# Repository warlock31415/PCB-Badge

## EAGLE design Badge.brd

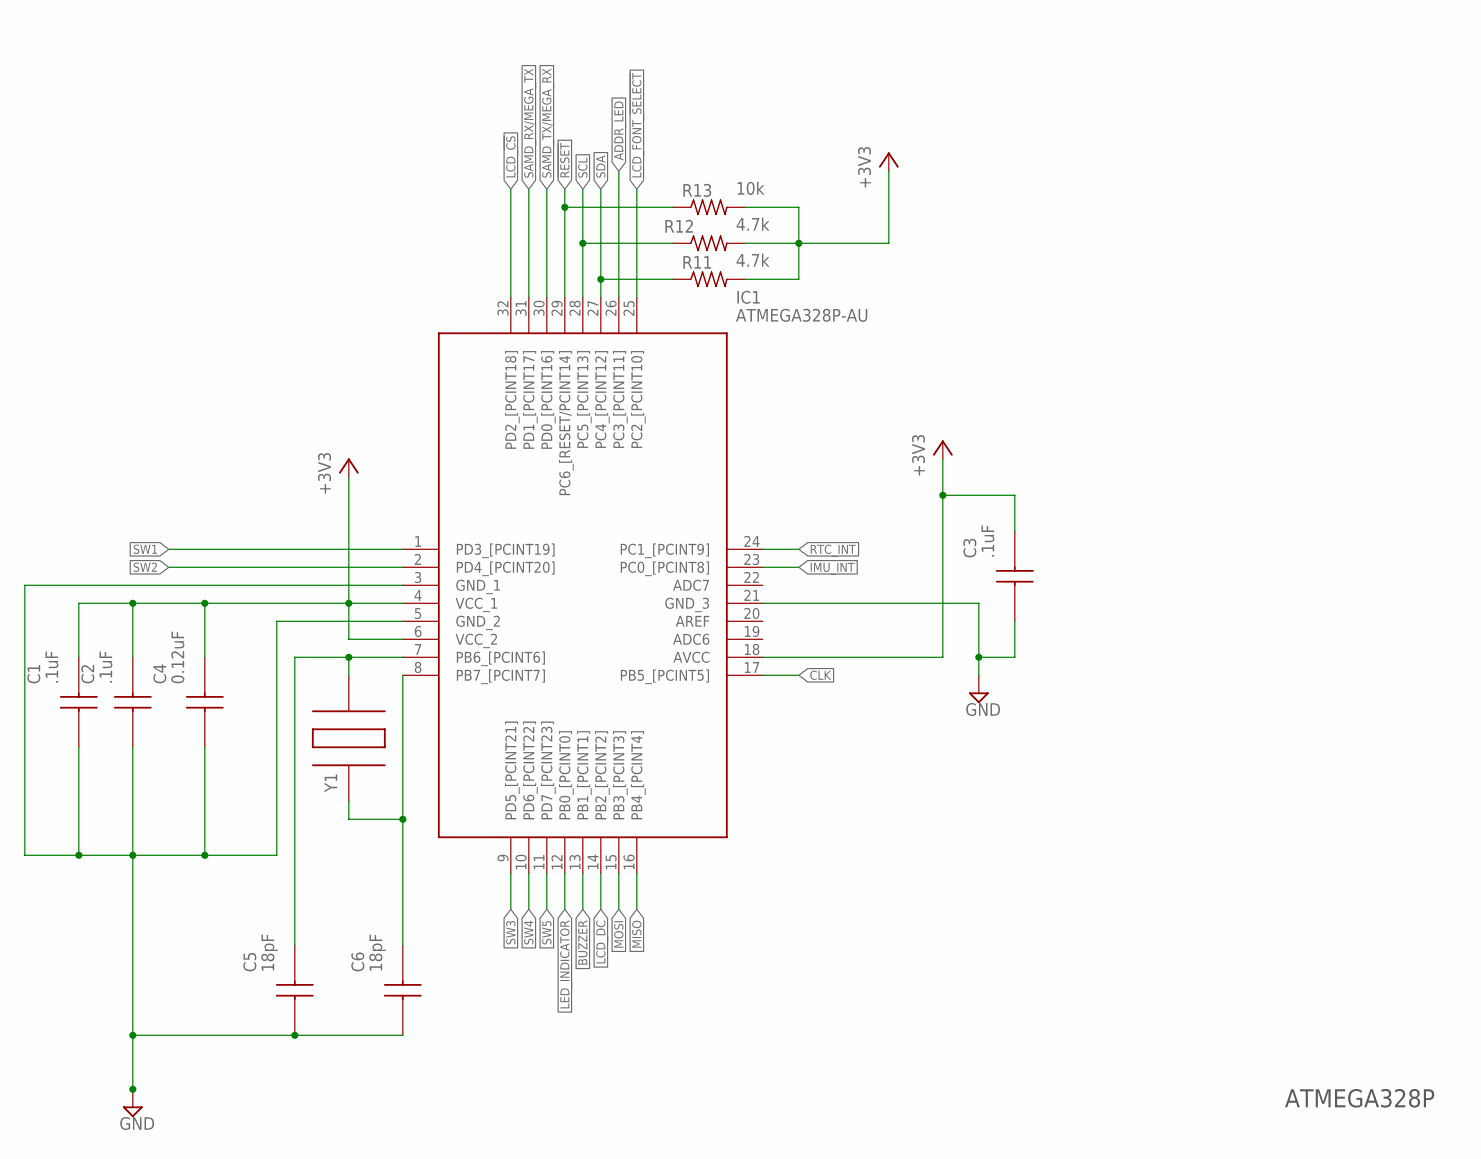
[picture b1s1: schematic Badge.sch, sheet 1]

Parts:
C1, C2, C3: .1uF; CAPC1608X87N
C4: 0.12uF; CAPC2013X94N
C5, C6: 18pF; CAPC1608X87N
IC1: ATMEGA328P-AU; QFP80P900X900X120-32N
R11: 4.7k; R0603; MANUFACTURER_PART_NUMBER o RC0603JR-074K7L
R12: 4.7k; R0603
R13: 10k; R0603; MANUFACTURER_PART_NUMBER RC0603JR-0710KL
Y1: ABM3-16.000MHZ-B2-T; ABM-3

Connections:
!RESET!: IC1.29 (PC6_[RESET/PCINT14]), R13.1; also elsewhere on the board
+3V3: C1.2, C2.2, C3.2, C4.2 (C2), IC1.4 (VCC_1), IC1.6 (VCC_2), IC1.18 (AVCC), R11.2, R12.2, R13.2; also elsewhere on the board
ADDR_LED: IC1.26 (PC3_[PCINT11]); also elsewhere on the board
BUZZER: IC1.13 (PB1_[PCINT1]); also elsewhere on the board
CLK: IC1.17 (PB5_[PCINT5])
GND: C1.1, C2.1, C3.1, C4.1 (C1), C5.1, C6.1, IC1.3 (GND_1), IC1.5 (GND_2), IC1.21 (GND_3); also elsewhere on the board
IMU_INT: IC1.23 (PC0_[PCINT8]); also elsewhere on the board
LCD_!CS!: IC1.32 (PD2_[PCINT18])
LCD_DC: IC1.14 (PB2_[PCINT2])
LCD_FONT_!SELECT!: IC1.25 (PC2_[PCINT10])
LED_INDICATOR: IC1.12 (PB0_[PCINT0]); also elsewhere on the board
MISO: IC1.16 (PB4_[PCINT4])
MOSI: IC1.15 (PB3_[PCINT3])
unnamed: C5.2, IC1.7 (PB6_[PCINT6]), Y1.2
unnamed: C6.2, IC1.8 (PB7_[PCINT7]), Y1.1
RTC_INT: IC1.24 (PC1_[PCINT9]); also elsewhere on the board
SAMD_RX/MEGA_TX: IC1.31 (PD1_[PCINT17]); also elsewhere on the board
SAMD_TX/MEGA_RX: IC1.30 (PD0_[PCINT16]); also elsewhere on the board
SCL: IC1.28 (PC5_[PCINT13]), R12.1; also elsewhere on the board
SDA: IC1.27 (PC4_[PCINT12]), R11.1; also elsewhere on the board
SW1: IC1.1 (PD3_[PCINT19]); also elsewhere on the board
SW2: IC1.2 (PD4_[PCINT20]); also elsewhere on the board
SW3: IC1.9 (PD5_[PCINT21]); also elsewhere on the board
SW4: IC1.10 (PD6_[PCINT22]); also elsewhere on the board
SW5: IC1.11 (PD7_[PCINT23]); also elsewhere on the board

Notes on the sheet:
ATMEGA328P

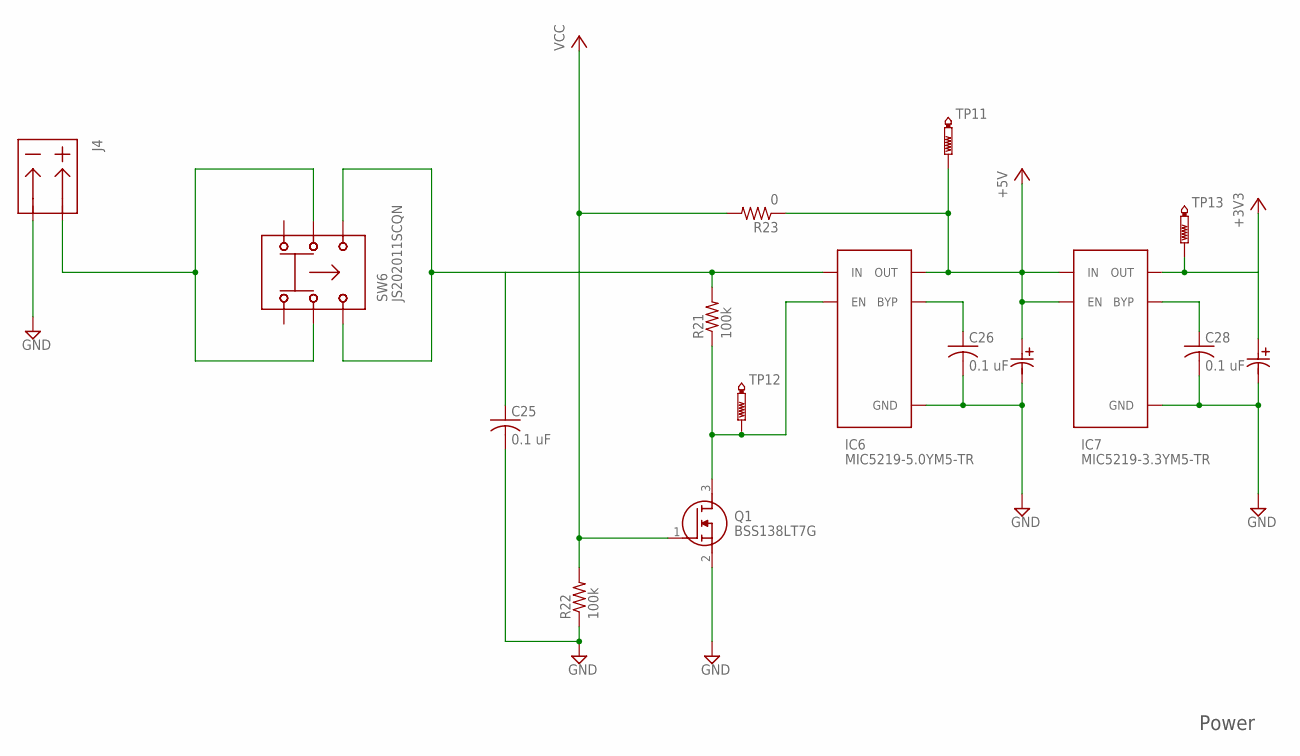
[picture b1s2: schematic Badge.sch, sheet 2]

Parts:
C25, C26, C28: 0.1 uF; C0603K
C27, C29: 22uF 16V 4.3mm; CAPAE430X550L180X65N
IC6: MIC5219-5.0YM5-TR; SOT23-5P95_280X145L45X37N
IC7: MIC5219-3.3YM5-TR; SOT23-5P95_280X145L45X37N
J4: DNP; BATIN
Q1: BSS138LT7G; SOT96P237X111-3N
R21, R22: 100k; R0603
R23: 0; R0603
SW6: JS202011SCQN
TP11, TP12, TP13: PTR1PAD1-20; P1-20

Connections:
+5V: C27.1 (PLUS), IC6.5 (OUT), IC7.1 (IN), IC7.3 (EN), R23.1, TP11.TP; also elsewhere on the board
+5V1: C29.1 (PLUS), IC7.5 (OUT), TP13.TP
GND: C25.2, C26.2, C27.2 (MINUS), C28.2, C29.2 (MINUS), IC6.2 (GND), IC7.2 (GND), J4.2, Q1.2 (S), R22.1; also elsewhere on the board
unnamed: C26.1, IC6.4 (BYP)
unnamed: C28.1, IC7.4 (BYP)
unnamed: J4.1, SW6.2, SW6.5
unnamed: C25.1, IC6.1 (IN), R21.2, SW6.3, SW6.6
unnamed: IC6.3 (EN), Q1.3 (D), R21.1, TP12.TP
VCC: Q1.1 (G), R22.2, R23.2

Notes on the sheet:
Power

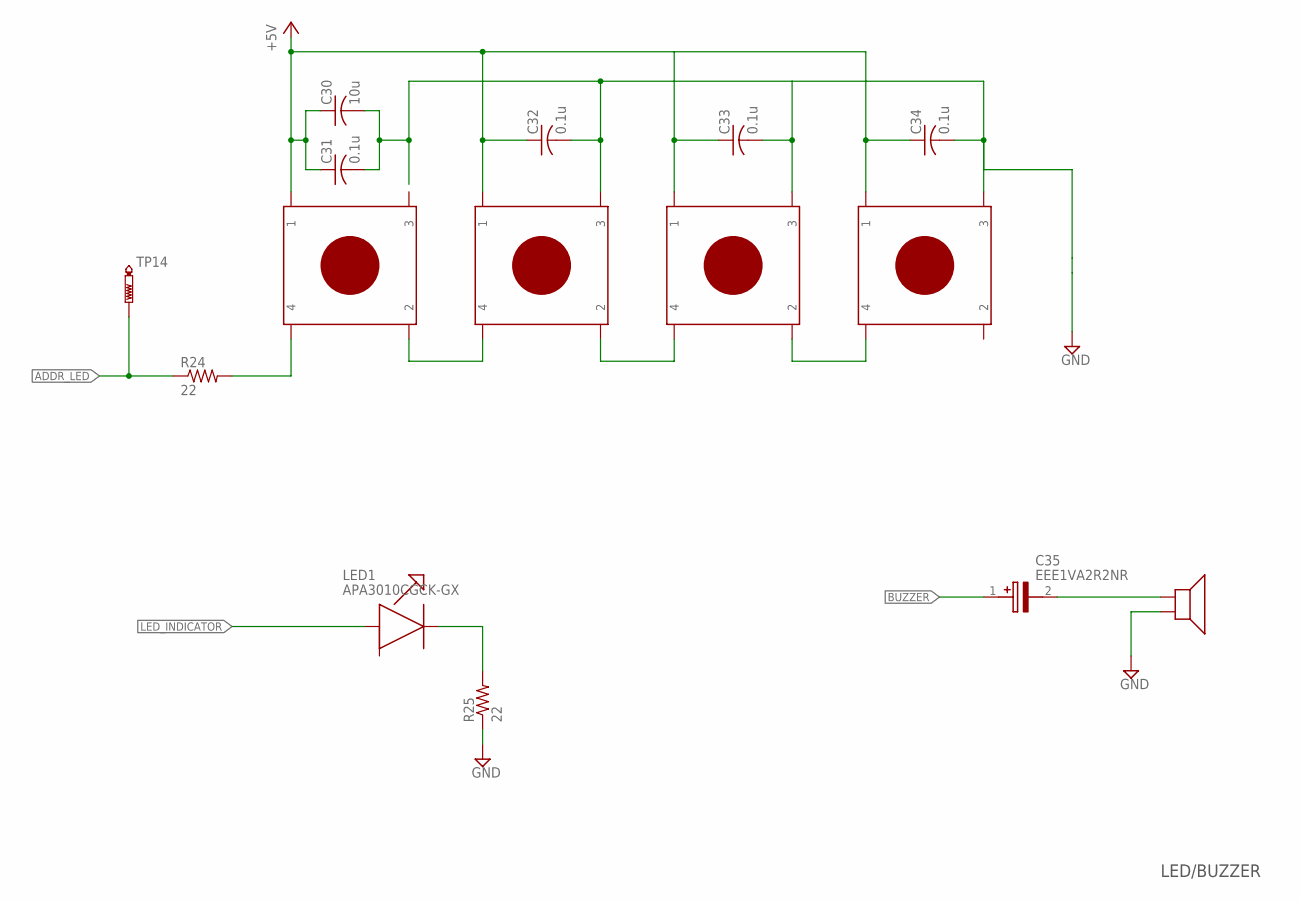
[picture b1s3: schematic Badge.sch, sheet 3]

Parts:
C30: 10u; C0805K
C31, C32, C33, C34: 0.1u; C0603K
C35: EEE1VA2R2NR; CAPAE430X550N
D2, D3, D4, D5: WS2812B
LED1: APA3010CGCK-GX; APA3010ZGCGX
LS1: AST-03008MR-R; PUIAUDIO_AST-03008MR-R
R24, R25: 22; R0603
TP14: PTR1PAD1-20; P1-20

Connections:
+5V: C30.1, C31.1, C32.1, C33.1, C34.1, D2.1, D3.1, D4.1, D5.1; also elsewhere on the board
ADDR_LED: R24.1, TP14.TP; also elsewhere on the board
BUZZER: C35.1 (+); also elsewhere on the board
GND: C30.2, C31.2, C32.2, C33.2, C34.2, D3.3, D4.3, D5.3, LS1.2, R25.1; also elsewhere on the board
LED_INDICATOR: LED1.2 (A); also elsewhere on the board
unnamed: C35.2 (-), LS1.1
unnamed: LED1.1 (K), R25.2
unnamed: D2.2, D3.4
unnamed: D3.2, D4.4
unnamed: D4.2, D5.4
unnamed: D2.4, R24.2

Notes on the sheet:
LED/BUZZER

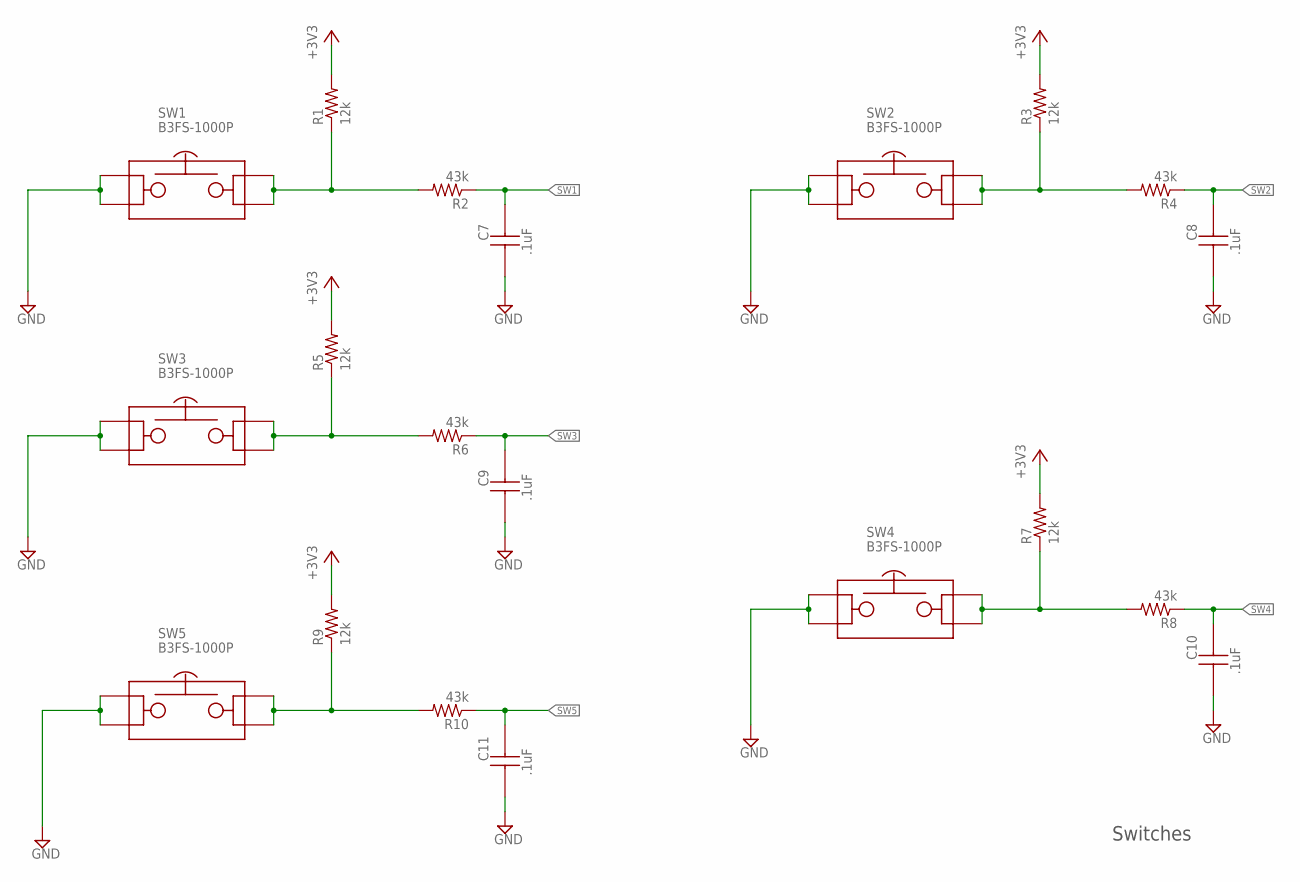
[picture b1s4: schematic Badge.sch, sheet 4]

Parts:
C7, C8, C9, C10, C11: .1uF; CAPC1608X87N
R1, R3, R5, R7, R9: 12k; R0603; MANUFACTURER_PART_NUMBER RC0603JR-0712KL
R2, R4, R6, R8, R10: 43k; R0603; MANUFACTURER_PART_NUMBER RC0603JR-0743KL
SW1, SW2, SW3, SW4, SW5: B3FS-1000P

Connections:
+3V3: R1.2, R3.2, R5.2, R7.2, R9.2; also elsewhere on the board
GND: C7.1, C8.1, C9.1, C10.1, C11.1, SW1.P$1, SW1.P$2, SW2.P$1, SW2.P$2, SW3.P$1, SW3.P$2, SW4.P$1, SW4.P$2, SW5.P$1, SW5.P$2; also elsewhere on the board
unnamed: R1.1, R2.2, SW1.P$3, SW1.P$4
unnamed: R5.1, R6.2, SW3.P$3, SW3.P$4
unnamed: R7.1, R8.2, SW4.P$3, SW4.P$4
unnamed: R3.1, R4.2, SW2.P$3, SW2.P$4
unnamed: R9.1, R10.2, SW5.P$3, SW5.P$4
SW1: C7.2, R2.1; also elsewhere on the board
SW2: C8.2, R4.1; also elsewhere on the board
SW3: C9.2, R6.1; also elsewhere on the board
SW4: C10.2, R8.1; also elsewhere on the board
SW5: C11.2, R10.1; also elsewhere on the board

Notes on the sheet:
Switches

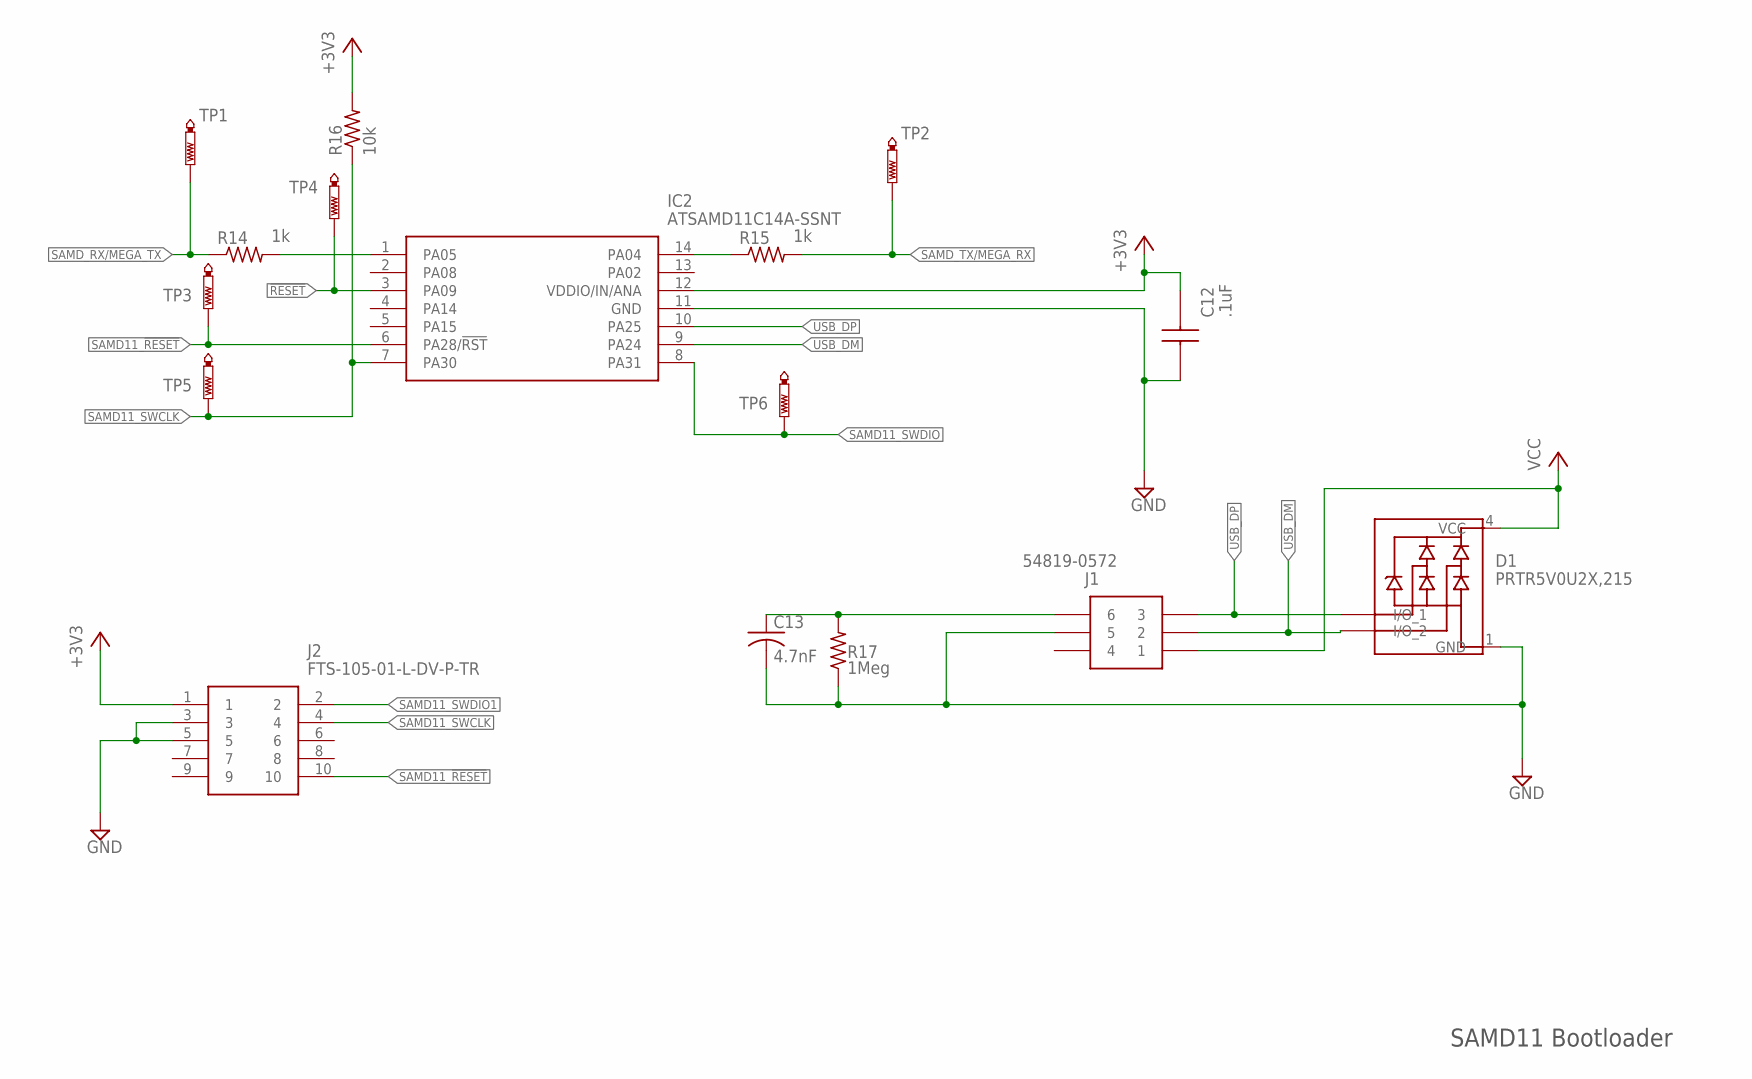
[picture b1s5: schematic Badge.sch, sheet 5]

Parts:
C12: .1uF; CAPC1608X87N
C13: 4.7nF; C0805K
D1: PRTR5V0U2X,215; SOT-143B
IC2: ATSAMD11C14A-SSNT; SOIC127P600X175-14N
J1: 54819-0572; MOLEXMINIBTYPEB_1
J2: FTS-105-01-L-DV-P-TR; FTS10501LDVPTR
R14, R15: 1k; R0603; MANUFACTURER_PART_NUMBER RC0603JR-0710KL
R16: 10k; R0603; MANUFACTURER_PART_NUMBER RC0603JR-0710KL
R17: 1Meg; R0603
TP1, TP2, TP3, TP4, TP5, TP6: PTR1PAD1-20; P1-20

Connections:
!RESET!: IC2.3 (PA09), TP4.TP; also elsewhere on the board
+3V3: C12.2, IC2.12 (VDDIO/IN/ANA), J2.1, R16.2; also elsewhere on the board
GND: C12.1, C13.2, D1.1 (GND), IC2.11 (GND), J1.5, J2.3, J2.5, R17.1; also elsewhere on the board
unnamed: IC2.14 (PA04), R15.1
unnamed: IC2.1 (PA05), R14.2
unnamed: C13.1, J1.6, J1.7 (6), J1.8 (6), J1.9 (6), R17.2
SAMD11_!RESET!: IC2.6 (PA28/!RST), J2.10, TP3.TP
SAMD11_SWCLK: IC2.7 (PA30), J2.4, R16.1, TP5.TP
SAMD11_SWDIO: IC2.8 (PA31), TP6.TP
SAMD11_SWDIO1: J2.2
SAMD_RX/MEGA_TX: R14.1, TP1.TP; also elsewhere on the board
SAMD_TX/MEGA_RX: R15.2, TP2.TP; also elsewhere on the board
USB_DM: D1.3 (I/O_2), IC2.9 (PA24), J1.2
USB_DP: D1.2 (I/O_1), IC2.10 (PA25), J1.3
V_USB: D1.4 (VCC), J1.1

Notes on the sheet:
SAMD11 Bootloader

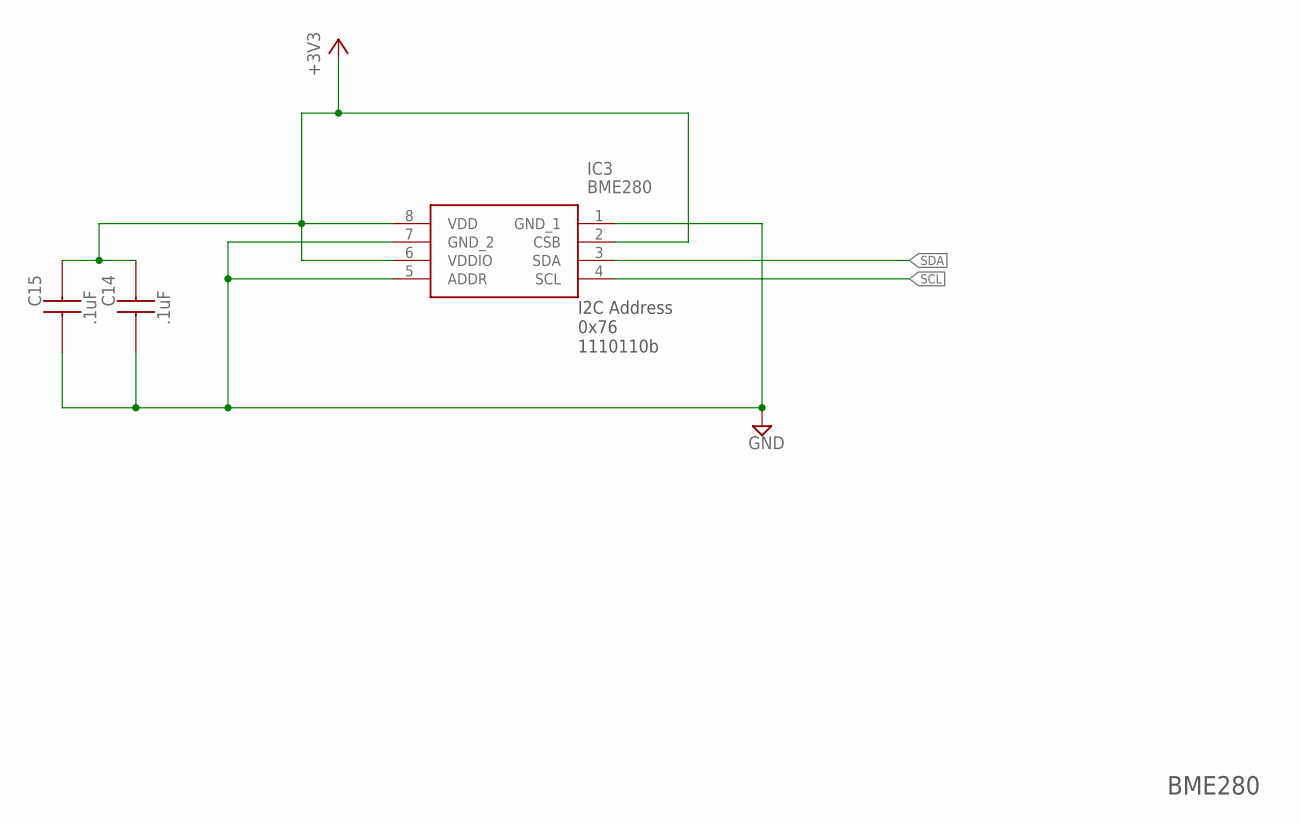
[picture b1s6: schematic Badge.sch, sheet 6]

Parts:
C14, C15: .1uF; CAPC1608X87N
IC3: BME280

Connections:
+3V3: C14.2, C15.2, IC3.2 (CSB), IC3.6 (VDDIO), IC3.8 (VDD); also elsewhere on the board
GND: C14.1, C15.1, IC3.1 (GND_1), IC3.5 (ADDR), IC3.7 (GND_2); also elsewhere on the board
SCL: IC3.4 (SCL); also elsewhere on the board
SDA: IC3.3 (SDA); also elsewhere on the board

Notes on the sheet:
I2C Address 0x76 1110110b
BME280

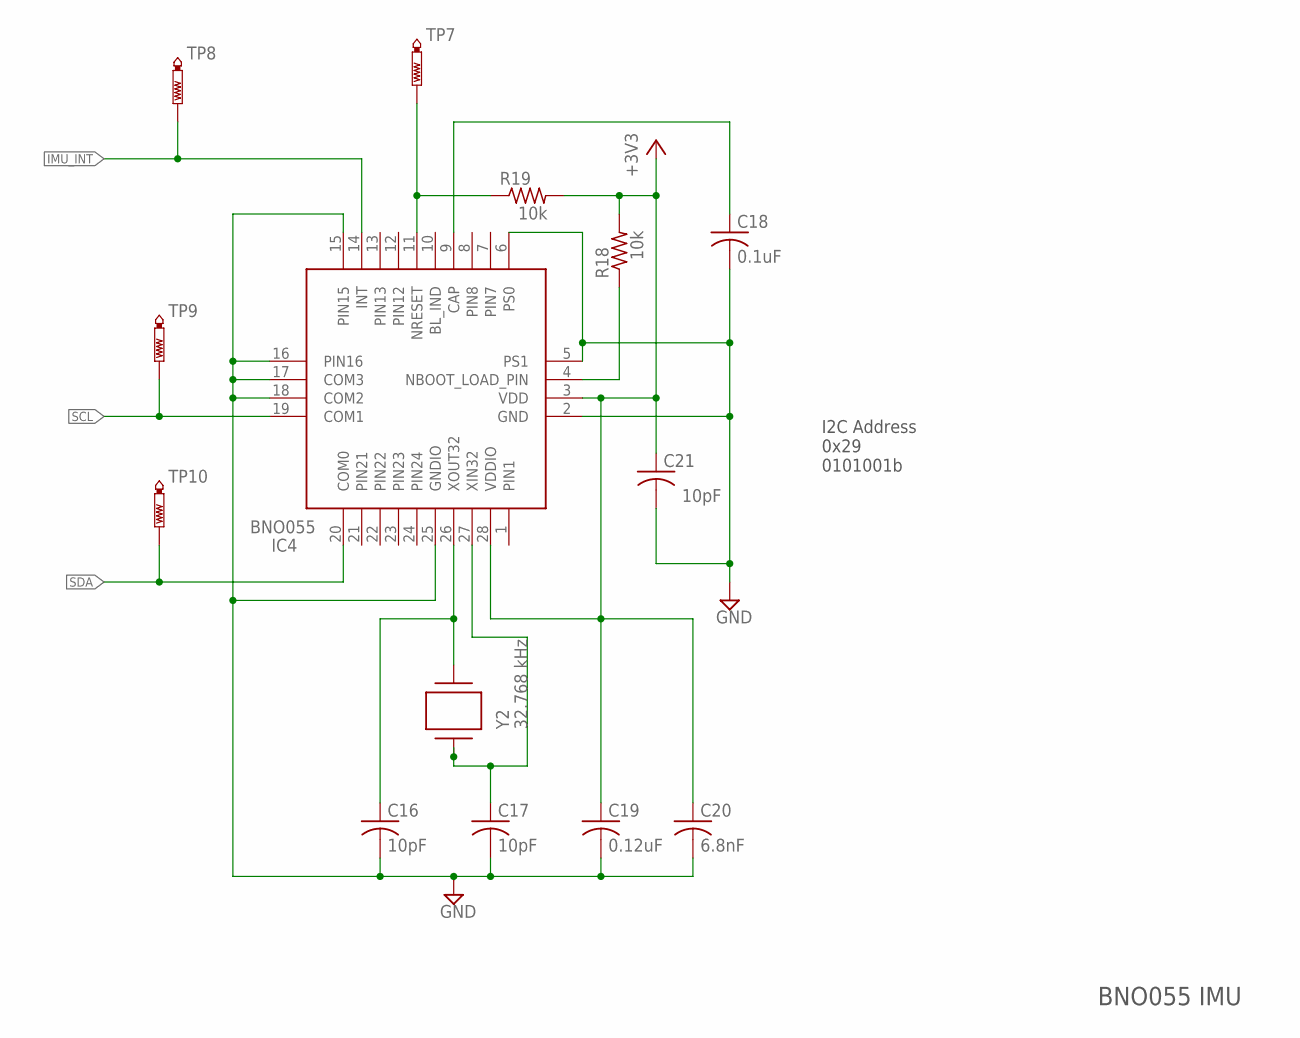
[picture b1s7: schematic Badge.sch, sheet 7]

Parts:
C16, C17, C21: 10pF; C0603K
C18: 0.1uF; C0603K
C19: 0.12uF; C0603K
C20: 6.8nF; C0603K
IC4: BNO055
R18, R19: 10k; R0603; MANUFACTURER_PART_NUMBER RC0603JR-0710KL
TP7, TP8, TP9, TP10: PTR1PAD1-20; P1-20
Y2: 32.768 kHz; XTAL960X406X315

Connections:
+3V3: C19.1, C20.1, C21.1, IC4.3 (VDD), IC4.28 (VDDIO), R18.2, R19.2; also elsewhere on the board
GND: C16.2, C17.2, C18.2, C19.2, C20.2, C21.2, IC4.2 (GND), IC4.5 (PS1), IC4.6 (PS0), IC4.15 (PIN15), IC4.16 (PIN16), IC4.17 (COM3), IC4.18 (COM2), IC4.25 (GNDIO); also elsewhere on the board
IMU_INT: IC4.14 (INT), TP8.TP; also elsewhere on the board
unnamed: C16.1, IC4.26 (XOUT32), Y2.1
unnamed: C17.1, IC4.27 (XIN32), Y2.2
unnamed: C18.1, IC4.9 (CAP)
unnamed: IC4.4 (NBOOT_LOAD_PIN), R18.1
unnamed: IC4.11 (NRESET), R19.1, TP7.TP
SCL: IC4.19 (COM1), TP9.TP; also elsewhere on the board
SDA: IC4.20 (COM0), TP10.TP; also elsewhere on the board

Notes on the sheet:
I2C Address 0x29 0101001b
BNO055 IMU

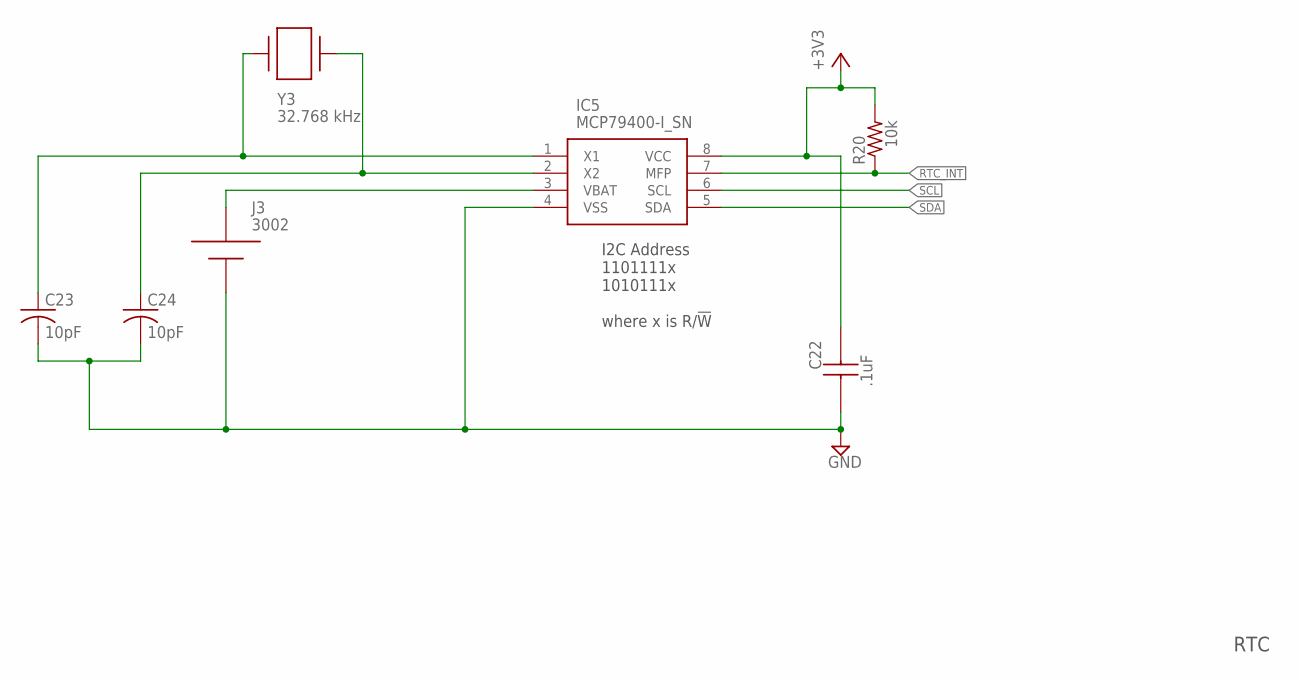
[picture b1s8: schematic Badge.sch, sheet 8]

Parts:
C22: .1uF; CAPC1608X87N
C23, C24: 10pF; C0603K
IC5: MCP79400-I_SN; SOIC127P600X175-8N
J3: 3002; SMT_CELL_HOLDER
R20: 10k; R0603; MANUFACTURER_PART_NUMBER RC0603JR-0710KL
Y3: 32.768 kHz; XTAL960X406X315

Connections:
+3V3: C22.2, IC5.8 (VCC), R20.2; also elsewhere on the board
GND: C22.1, C23.2, C24.2, IC5.4 (VSS), J3.2 (NEG); also elsewhere on the board
unnamed: IC5.3 (VBAT), J3.1 (POS_1), J3.3 (POS_1)
unnamed: C23.1, IC5.1 (X1), Y3.2
unnamed: C24.1, IC5.2 (X2), Y3.1
RTC_INT: IC5.7 (MFP), R20.1; also elsewhere on the board
SCL: IC5.6 (SCL); also elsewhere on the board
SDA: IC5.5 (SDA); also elsewhere on the board

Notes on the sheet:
I2C Address 1101111x 1010111x where x is R/!W!
RTC

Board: 2 copper layers, 102 parts (0 on the bottom side), 55 nets, no tracks yet.

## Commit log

2020-04-06 Initial Commit
    Need to add power, LED/Buzzer,LCD sheets
2020-04-10 Added Power and LEDs
    Also added a new library.
